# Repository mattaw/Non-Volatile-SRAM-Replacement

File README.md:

# XX62-SRAM-non-volatile-replacement
XX62 SRAM non-volatile replacement HP3457A

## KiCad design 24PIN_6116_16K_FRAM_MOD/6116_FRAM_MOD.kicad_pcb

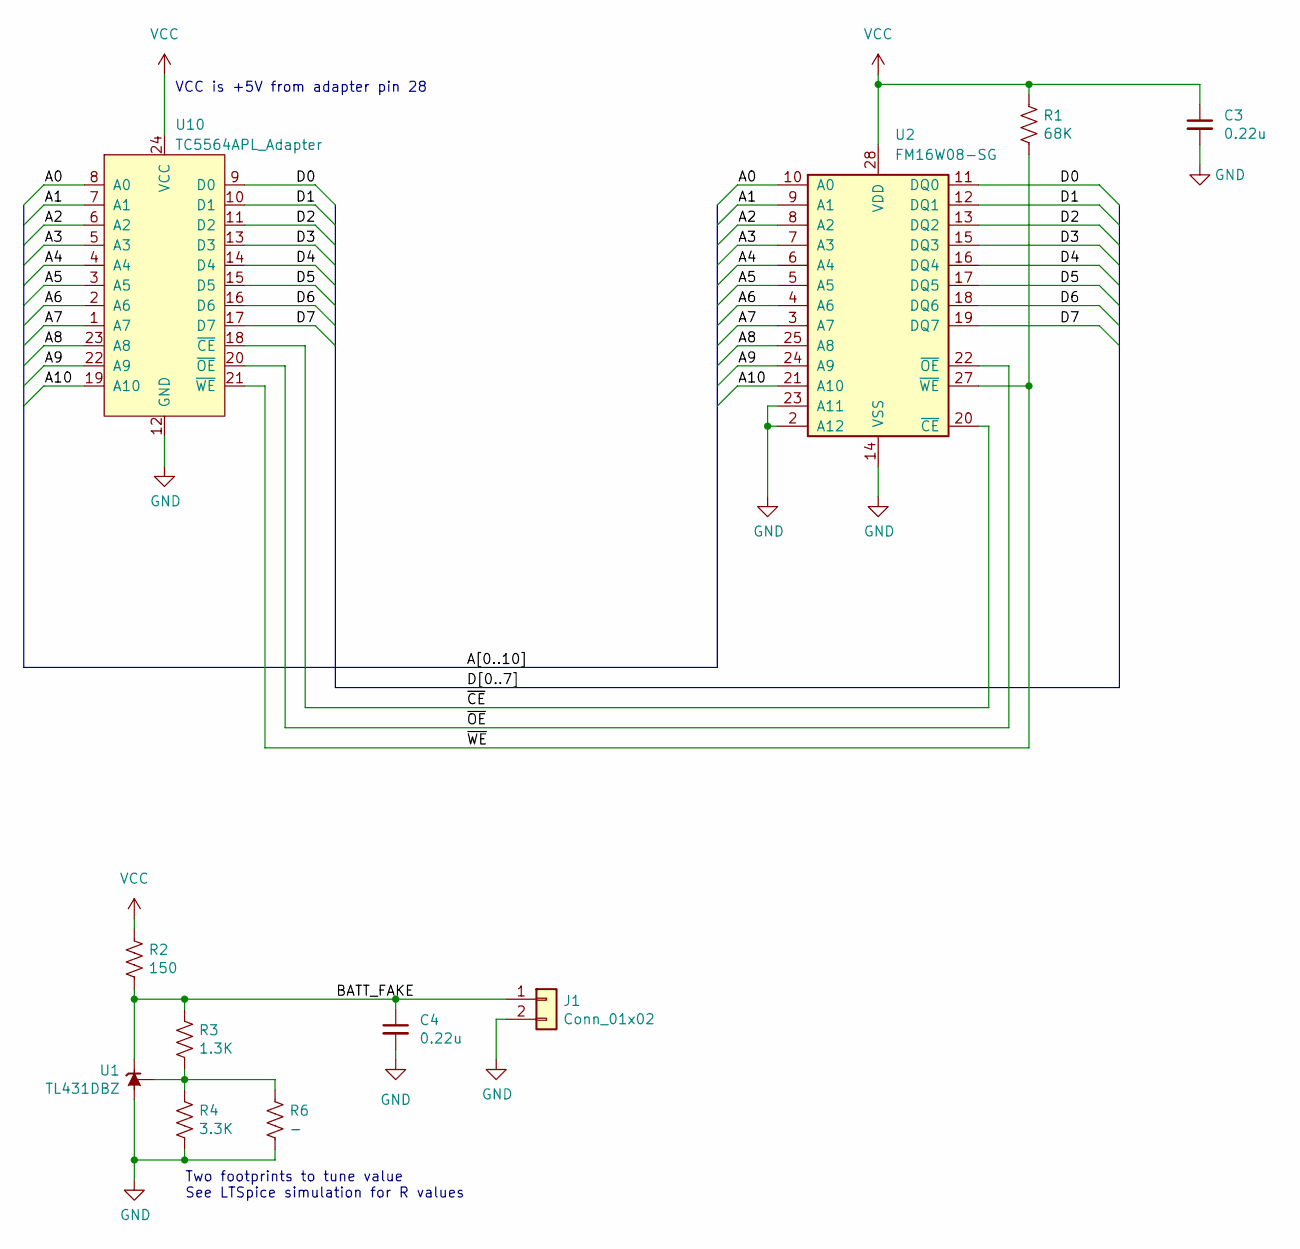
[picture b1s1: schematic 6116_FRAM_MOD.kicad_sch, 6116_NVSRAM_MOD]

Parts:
C3, C4: 0.22u; C_0603_1608Metric; MPN CC0603ZRY5V8BB104; Digikey 1276-1111-2-ND
J1: Conn_01x02; JST_PH_B2B-PH-K_1x02_P2.00mm_Vertical; MPN XX62 nvSRAM V1
R1: 68K; R_0402_1005Metric_Pad0.72x0.64mm_HandSolder
R2: 150; R_0402_1005Metric_Pad0.72x0.64mm_HandSolder
R3: 1.3K; R_0402_1005Metric_Pad0.72x0.64mm_HandSolder
R4: 3.3K; R_0402_1005Metric_Pad0.72x0.64mm_HandSolder
R6: -; R_0402_1005Metric_Pad0.72x0.64mm_HandSolder
U1: TL431DBZ; SOT-23; MPN ZTL431AFTA; Digikey ZTL431AFCT-ND
U2: FM16W08-SG; SOIC-28W_7.5x17.9mm_P1.27mm
U10: TC5564APL_Adapter; DIP-24_W15.24mm_Socket_Adapter

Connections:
/A0: U2.10 (A0), U10.8 (A0)
/A1: U2.9 (A1), U10.7 (A1)
/A2: U2.8 (A2), U10.6 (A2)
/A3: U2.7 (A3), U10.5 (A3)
/A4: U2.6 (A4), U10.4 (A4)
/A5: U2.5 (A5), U10.3 (A5)
/A6: U2.4 (A6), U10.2 (A6)
/A7: U2.3 (A7), U10.1 (A7)
/A8: U2.25 (A8), U10.23 (A8)
/A9: U2.24 (A9), U10.22 (A9)
/A10: U2.21 (A10), U10.19 (A10)
/BATT_FAKE: C4.1, J1.1, R2.2, R3.1, U1.1 (K)
/D0: U2.11 (DQ0), U10.9 (D0)
/D1: U2.12 (DQ1), U10.10 (D1)
/D2: U2.13 (DQ2), U10.11 (D2)
/D3: U2.15 (DQ3), U10.13 (D3)
/D4: U2.16 (DQ4), U10.14 (D4)
/D5: U2.17 (DQ5), U10.15 (D5)
/D6: U2.18 (DQ6), U10.16 (D6)
/D7: U2.19 (DQ7), U10.17 (D7)
/~CE: U2.20 (~CE), U10.18 (~CE)
/~OE: U2.22 (~OE), U10.20 (~OE)
/~WE: R1.2, U2.27 (~WE), U10.21 (~WE)
GND: C3.2, C4.2, J1.2, R4.2, R6.2, U1.3 (A), U2.2 (A12), U2.14 (VSS), U2.23 (A11), U10.12 (GND)
unnamed: R3.2, R4.1, R6.1, U1.2 (REF)
VCC: C3.1, R1.1, R2.1, U2.28 (VDD), U10.24 (VCC)

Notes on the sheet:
VCC is +5V from adapter pin 28
Two footprints to tune value See LTSpice simulation for R values

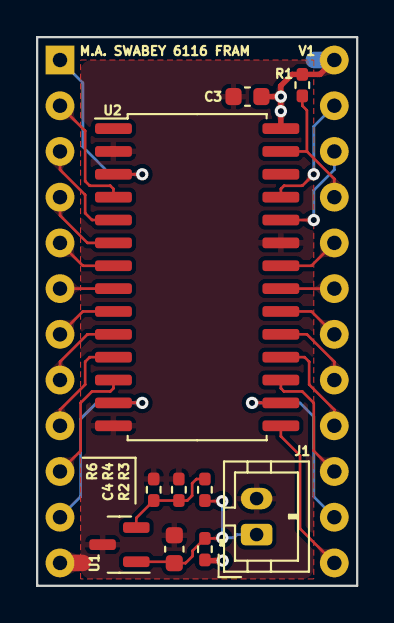
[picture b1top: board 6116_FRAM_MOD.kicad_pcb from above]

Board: 2 copper layers, 17.8 x 30.5 mm, 11 parts (0 on the bottom side), 26 nets.

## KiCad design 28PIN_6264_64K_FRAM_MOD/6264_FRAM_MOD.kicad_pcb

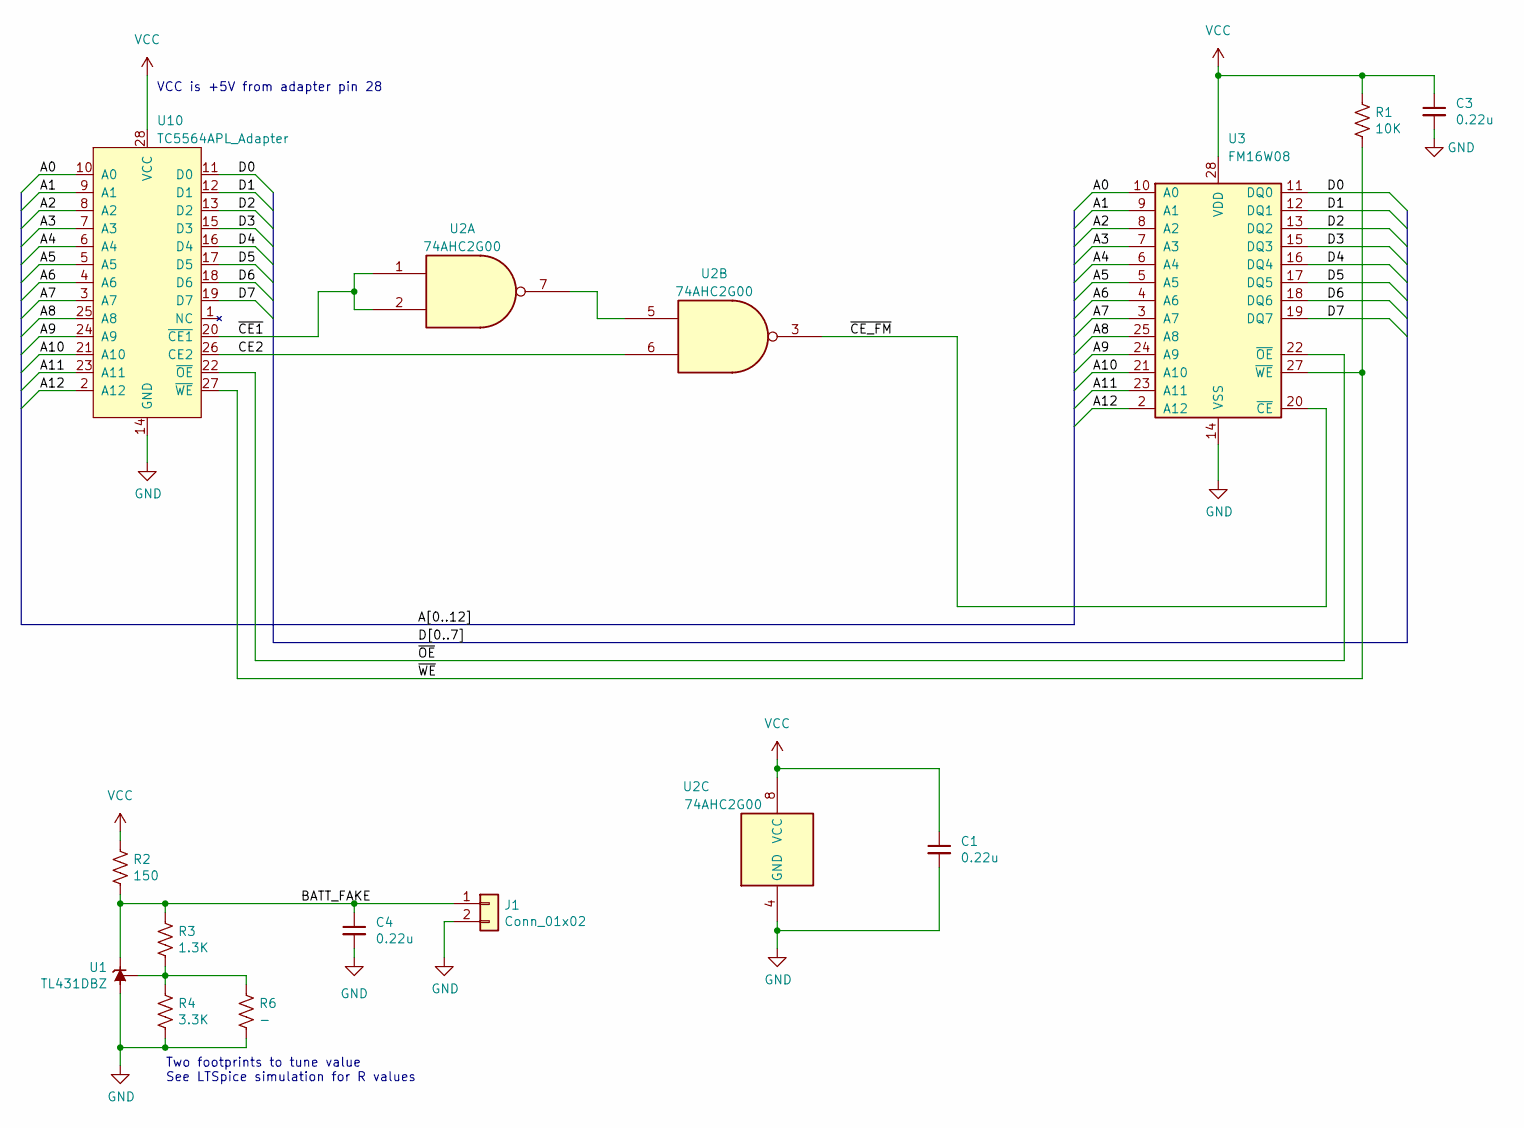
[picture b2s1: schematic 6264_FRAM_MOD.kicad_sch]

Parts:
C1, C3, C4: 0.22u; C_0603_1608Metric; MPN CC0603ZRY5V8BB104; Digikey 1276-1111-2-ND
J1: Conn_01x02; JST_PH_B2B-PH-K_1x02_P2.00mm_Vertical; MPN XX62 nvSRAM V1
R1: 10K; R_0402_1005Metric_Pad0.72x0.64mm_HandSolder
R2: 150; R_0402_1005Metric_Pad0.72x0.64mm_HandSolder
R3: 1.3K; R_0402_1005Metric_Pad0.72x0.64mm_HandSolder
R4: 3.3K; R_0402_1005Metric_Pad0.72x0.64mm_HandSolder
R6: -; R_0402_1005Metric_Pad0.72x0.64mm_HandSolder
U1: TL431DBZ; SOT-23; MPN ZTL431AFTA; Digikey ZTL431AFCT-ND
U2: 74AHC2G00; TSSOP-8_3x3mm_P0.65mm
U3: FM16W08; SOIC-28W_7.5x17.9mm_P1.27mm
U10: TC5564APL_Adapter; DIP-28_W15.24mm_Socket_Adapter

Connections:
/A0: U3.10 (A0), U10.10 (A0)
/A1: U3.9 (A1), U10.9 (A1)
/A2: U3.8 (A2), U10.8 (A2)
/A3: U3.7 (A3), U10.7 (A3)
/A4: U3.6 (A4), U10.6 (A4)
/A5: U3.5 (A5), U10.5 (A5)
/A6: U3.4 (A6), U10.4 (A6)
/A7: U3.3 (A7), U10.3 (A7)
/A8: U3.25 (A8), U10.25 (A8)
/A9: U3.24 (A9), U10.24 (A9)
/A10: U3.21 (A10), U10.21 (A10)
/A11: U3.23 (A11), U10.23 (A11)
/A12: U3.2 (A12), U10.2 (A12)
/BATT_FAKE: C4.1, J1.1, R2.2, R3.1, U1.1 (K)
/CE2: U2.6, U10.26 (CE2)
/D0: U3.11 (DQ0), U10.11 (D0)
/D1: U3.12 (DQ1), U10.12 (D1)
/D2: U3.13 (DQ2), U10.13 (D2)
/D3: U3.15 (DQ3), U10.15 (D3)
/D4: U3.16 (DQ4), U10.16 (D4)
/D5: U3.17 (DQ5), U10.17 (D5)
/D6: U3.18 (DQ6), U10.18 (D6)
/D7: U3.19 (DQ7), U10.19 (D7)
/~CE1: U2.1, U2.2, U10.20 (~CE1)
/~CE_FM: U2.3, U3.20 (~CE)
/~OE: U3.22 (~OE), U10.22 (~OE)
/~WE: R1.2, U3.27 (~WE), U10.27 (~WE)
GND: C1.2, C3.2, C4.2, J1.2, R4.2, R6.2, U1.3 (A), U2.4 (GND), U3.14 (VSS), U10.14 (GND)
unnamed: R3.2, R4.1, R6.1, U1.2 (REF)
unnamed: U2.5, U2.7
VCC: C1.1, C3.1, R1.1, R2.1, U2.8 (VCC), U3.28 (VDD), U10.28 (VCC)

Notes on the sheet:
VCC is +5V from adapter pin 28
Two footprints to tune value See LTSpice simulation for R values

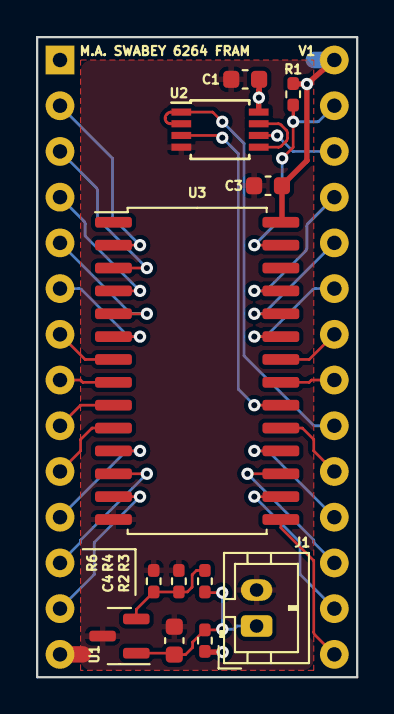
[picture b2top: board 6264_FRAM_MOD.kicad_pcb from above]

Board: 2 copper layers, 17.8 x 35.6 mm, 13 parts (0 on the bottom side), 31 nets.

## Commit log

2022-10-25 Excluded backups as we are using Git
2022-10-25 Adding LFS support for large PDF files.
2022-10-25 First commit of board and files
2022-10-28 Added LTSpice support
2022-10-28 Added pictures and archive of webpage detailling modifications.
2022-10-28 Added in LTSpice simulation of TL431 regulator.
2022-10-28 Moved to 0402 resistors, tweaked pours, minor cleanups.
2022-10-28 Design tweaked and gerbers submitted to OSHPark V1
2022-11-03 Updated to KiCAD 6.09. Excluded Vcc - 5V warning.
2022-11-03 Added VCAP app note to references.
2022-11-03 Version submitted to OSHPark as V1
2022-11-03 Rechecked PCB in Kicad 6.09, all fine.
2022-11-09 Improved labelling and checked board in new KiCad version.
2022-11-10 Renamed prior to move
2022-11-10 Moved to subdir and renamed to XX62
2022-11-12 Renamed projects w. generic ram terminology - 28PIN_6264_
2022-11-12 Added 24 pin 6116 16K datasheets and 6264 64K datasheets.
2022-11-12 Final commit of project rename - probably should be merged with existing commits.
2022-11-12 Updated silkscreen w. new naming scheme.
2022-11-12 Excluded all *-backups/ subdirs
2022-11-12 Updated silkscreen to correct name 6264
2022-11-12 Finished 24PIN 6116 version.
2022-11-18 Updated title block on schematics. Minor silkscreen tweak to 24PIN 6116
2022-12-20 Minor tweak to align silkscreen. Note that 6112 mod needs smaller footprint w. no caps for FRAM support.
2022-12-20 Cleaned up some tiny offsets and a silkscreen bobble in 6264 NVSRAM board. Regenerated Gerbers.
2022-12-20 Added new FRAM only version of 6264
2023-04-06 Updated to KiCAD 7 and library updates.
2023-04-28 Removed Kicad6 plugin teardrops for 7 built in.

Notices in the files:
24PIN_6116_16K_FRAM_MOD/6116_FRAM_MOD.kicad_sch:
Copyright Dr. Matthew Swabey
